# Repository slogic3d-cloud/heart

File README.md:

# <3 LED-Herz

*A heart with a matrix led in heart form.*

Ein herzförmiges PCB mit **46 RGB-LEDs (WS2812B)**, das eine Lichtshow abspielt.
Ein Taster auf der Rückseite schaltet zwischen den Effekten um, Strom kommt per **USB-C**.
Gesteuert wird alles von einem **Seeed XIAO ESP32-C3**, der hinten aufgesteckt ist.

| | |
|---|---|
| Größe | ca. 162 × 153 mm, 2 Lagen, 1,6 mm |
| LEDs | 46 × WS2812B-5050, Raster 16 mm, je ein 100 nF Kondensator |
| Controller | Seeed XIAO ESP32-C3 (oder XIAO ESP32-S3, gleiche Pinbelegung) |
| Strom | USB-C 5 V (nur Strom), Software-Limit 1,5 A |
| Bedienung | 1 Taster: kurz = nächster Effekt, lang = Helligkeit |
| Effekte | Herzschlag, Regenbogen, Wellen, Glitzer, Feuer, Scanner, Konfetti, Auto |

## So funktioniert's

Das ist die vereinfachte Übersicht. Der **echte KiCad-Schaltplan** ist `hardware/heart.kicad_sch`
(als PDF: [docs/schematic.pdf](docs/schematic.pdf)), siehe [Schaltplan in KiCad](#schaltplan-in-kicad).

- **USB-C (J1)** liefert 5 V. Die zwei 5,1 kΩ an CC1/CC2 sagen dem Netzteil: „Ich will 5 V“.
- **+5V** liegt als Kupferfläche auf der ganzen Vorderseite, **GND** als Fläche auf der ganzen Rückseite.
  Dadurch kommen alle LEDs ohne dicke Leiterbahnen an genug Strom.
- Der **XIAO** bekommt seine 5 V über die Schottky-Diode **D47**. Dadurch kannst du den XIAO
  gleichzeitig am PC (zum Flashen) und am Netzteil haben, ohne dass der PC die LEDs versorgen muss.
- Der ESP32 gibt 3,3 V-Signale aus, die WS2812B wollen bei 5 V eigentlich ≥ 3,5 V sehen.
  Der **74AHCT1G125 (U1)** hebt das Datensignal sauber auf 5 V, **R1 (330 Ω)** dämpft die Leitung.
- Die LEDs hängen als **Kette** hintereinander: Start unten an der Spitze, dann in Schlangenlinien nach oben.
  Die Firmware kennt diese Reihenfolge (`src/heart_map.h`), damit Effekte wie „Feuer“ wirklich von unten nach oben laufen.

| Vorderseite (LEDs, +5V-Fläche) | Rückseite (GND-Fläche, XIAO, Taster, Elko) |
|---|---|
|  |  |

## Ordner

```
hardware/
  gen_pcb.py          erzeugt die komplette Platine per Skript (KiCad 7+)
  gen_sch.py          erzeugt den KiCad-Schaltplan
  netlist.py          Bauteil- und Netzliste (gemeinsame Basis für den Schaltplan)
  check_sch.py        prüft: Schaltplan und Platine passen Pin für Pin zusammen
  heart.kicad_pro     KiCad-Projekt – das hier öffnen
  heart.kicad_sch     der Schaltplan
  drc.py              Design-Rule-Check (prüft Abstände, Verbindungen)
  export.py           Gerber + BOM + CPL für JLCPCB
  heart.kicad_pcb     die Platine (mit KiCad öffnen)
  heart.pretty/       eigener Footprint für den XIAO-Sockel
  heart.kicad_sym     eigenes Symbol für den XIAO
  production/         fertige Bestelldateien (heart_gerber.zip, heart_bom.csv, heart_cpl.csv)
src/                  Firmware (PlatformIO / Arduino)
test/test_chain.cpp   prüft, dass Firmware und Platine dieselbe LED-Reihenfolge haben
tools/preview.html    Lichtshow im Browser ansehen, ganz ohne Hardware
cad/gen_case.py       erzeugt Gehäuse, Pixel-Gitter, Diffusor, Tasterstößel und Ständer (CadQuery)
cad/out/              STEP-Dateien für Fusion 360 + 3MF/STL-Dateien zum Drucken
docs/                 Bilder und Schaltplan
JOURNAL.md            Bau-Tagebuch
einkauf/              links.md (Kauflinks) und price.md (alle Preise in € und $), neu erzeugen: python3 tools/einkauf.py
```

**Was kostet das und wo kaufe ich es?** Siehe [einkauf/price.md](einkauf/price.md) (alle Preise in Euro und Dollar)
und [einkauf/links.md](einkauf/links.md) (Kauflinks: BerryBase, Amazon, JLCPCB).
Preise und Dollarkurs werden live abgefragt, mit `python3 tools/einkauf.py` aktualisierst du beides.

## 1. Platine bei JLCPCB bestellen

1. Auf [jlcpcb.com](https://jlcpcb.com) → **Order now** → `hardware/production/heart_gerber.zip` hochladen.
2. Einstellungen: **2 Layers**, Dicke **1.6 mm**, Farbe nach Wahl (Rot oder Schwarz sieht beim Herz gut aus),
   Surface Finish **HASL (lead free)** reicht.
3. Unten **PCB Assembly** einschalten → **Assemble top side**, Stückzahl z. B. 2 (Minimum bei Bestückung).
4. **BOM** = `hardware/production/heart_bom.csv`, **CPL** = `hardware/production/heart_cpl.csv` hochladen.
5. Im Bauteil-Check sollten alle 8 Positionen gefunden werden (LCSC-Nummern sind drin, geprüft im Oktober 2026):

   | Teil | Menge | LCSC |
   |---|---|---|
   | WS2812B-B/W (5050) | 46 | C114586 |
   | 100 nF 0603 | 47 | C14663 |
   | 10 µF 0805 | 1 | C15850 |
   | 5,1 kΩ 0603 | 2 | C23186 |
   | 330 Ω 0603 | 1 | C23138 |
   | SN74AHCT1G125DBVR | 1 | C7484 |
   | SS34 (SMA) | 1 | C408258 |
   | USB-C HRO TYPE-C-31-M-12 | 1 | C165948 |

6. **Ganz wichtig: Bestückungs-Vorschau anschauen!** JLCPCB zeigt die Bauteile über der Platine an.
   Bei manchen Bauteilen (oft LEDs, SOT-23, USB-C) dreht JLCPCB anders als KiCad.
   Prüfe vor allem:
   - **LEDs:** die abgeschrägte Ecke / Markierung muss bei **Pin 1** sein (im KiCad-Footprint die „1“ im Aufdruck).
   - **U1:** Pin 1 ist der Pin links oben, wenn die 2-Pin-Seite rechts ist.
   - **D47:** der Strich (Kathode) zeigt zum XIAO hin.
   Falsch gedrehte Teile kannst du direkt in der Vorschau drehen.
7. Preis: Die Platine ist größer als 10 × 10 cm und einige Bauteile sind „Extended Parts“
   (Bestückungsgebühr pro Bauteilsorte). Schau dir das Angebot genau an, bevor du bestellst.

### Was du selbst lötest (alles Durchsteck-Teile, auf der Rückseite)

| Teil | Wo | Hinweis |
|---|---|---|
| Seeed XIAO ESP32-C3 | U2 | mit 2 × 7-poligen Stiftleisten am XIAO |
| 2 × Buchsenleiste 1×7, 2,54 mm | U2 | auf die Platine löten, XIAO steckt drauf. **Bauteile des XIAO zeigen von der Platine weg, seine USB-C-Buchse zur Ausbuchtung im aufgedruckten Rahmen** |
| Taster 6 × 6 mm (THT) | SW1 „EFFEKT“ | |
| Elko 1000 µF (10 V oder mehr, z. B. 25 V), Ø 10 mm, Raster 5 mm, max. 20 mm hoch | C50 | **Polung!** Das eckige Pad ist Plus |

Tipp: Erst Buchsenleisten, dann Taster, zuletzt den Elko löten.

## 2. Firmware flashen

Mit [PlatformIO](https://platformio.org) (VS Code-Erweiterung oder `pip install platformio`):

```bash
pio run -e xiao_esp32c3 -t upload    # flashen
pio device monitor                   # Ausgabe ansehen (115200 Baud)
```

Falls der Upload nicht klappt: am XIAO **BOOT** gedrückt halten, **RESET** kurz drücken, BOOT loslassen, nochmal hochladen.

Mit der **Arduino IDE** geht es auch: Board „XIAO_ESP32C3“ auswählen, Bibliothek **FastLED** installieren,
alle Dateien aus `src/` in einen Sketch-Ordner `heart/` kopieren und `main.cpp` in `heart.ino` umbenennen.

Beim Einschalten läuft einmal ein Regenbogen durch alle 46 LEDs in Ketten-Reihenfolge.
Bleibt er an einer Stelle hängen, hat die LED davor oder genau diese ein Lötproblem.

## 3. Bedienung

- **Kurz drücken:** nächster Effekt. Nach „Konfetti“ kommt **Auto** (wechselt alle 15 s).
- **Lang drücken (0,8 s):** Helligkeit 24 → 64 → 128 → 200.
- Effekt und Helligkeit bleiben gespeichert, auch nach dem Ausstecken.

Einstellungen (Pins, Stromlimit, Helligkeitsstufen, Auto-Zeit) stehen in `src/config.h`.
Neue Effekte schreibst du in `src/effects.cpp` und trägst sie unten in `LIST` ein.

## 4. Effekte ohne Hardware ansehen

`tools/preview.html` im Browser öffnen. Die Vorschau benutzt dieselbe LED-Anordnung und dieselben Effekte.

| Regenbogen | Feuer |
|---|---|
|  |  |

## Schaltplan in KiCad

1. KiCad 7 oder neuer installieren ([kicad.org](https://www.kicad.org/download/)).
2. `hardware/heart.kicad_pro` öffnen. Im Projektfenster:
   - **Schaltplan-Editor** → `heart.kicad_sch` (ein A2-Blatt: oben Strom, XIAO, Pegelwandler; unten die 46 LEDs)
   - **Leiterplatten-Editor** → `heart.kicad_pcb`
3. Die Bibliotheken `heart` (XIAO-Symbol und -Footprint) sind über `sym-lib-table` / `fp-lib-table`
   im Projektordner eingebunden, da musst du nichts einstellen.

Verbunden wird im Schaltplan über **Netzlabels** (z. B. `LED5_DOUT`, `DATA_5V`) und die Power-Symbole
`+5V` / `GND`. Gleicher Name = gleiche Leitung. Die Namen sind exakt dieselben wie auf der Platine.

Schaltplan und Platine sind **verknüpft**. Wenn du im Schaltplan etwas änderst (z. B. einen Wert),
kannst du im Leiterplatten-Editor **Werkzeuge → Leiterplatte aus Schaltplan aktualisieren (F8)** drücken.
Geprüft wird das mit:

```bash
python3 hardware/check_sch.py   # "OK: Schaltplan und Platine stimmen überein"
```

KiCad 8/9 fragt beim Öffnen evtl., ob die Dateien ins neue Format umgewandelt werden sollen. Das ist ok.

## Gehäuse und Ständer (Fusion 360 / 3D-Druck)

| Im Ständer | Rückseite |
|---|---|
|  |  |

Alle Teile liegen in `cad/out/`, jeweils als **STEP** (für Fusion 360) und als **3MF** und **STL** (zum Drucken).
Die Druckdateien liegen schon flach auf dem Druckbett (Unterseite bei z = 0), die STEP-Dateien in Einbauposition.

| Datei | Teil | Material-Tipp |
|---|---|---|
| `heart_case_shell` | Rückschale mit Abstandshaltern, USB-C-Schlitz, Fenster fürs XIAO-Kabel, Tasterloch, 2 Schlüssellöchern | PLA/PETG, Farbe nach Wahl |
| `heart_case_grid` | Pixel-Gitter (16-mm-Raster, 10 mm tief), jede LED leuchtet in ihrem eigenen Quadrat | **schwarz**, damit kein Licht in die Nachbarzelle scheint |
| `heart_case_diffuser` | 1-mm-Platte vorne, macht aus den LED-Punkten gleichmäßige Pixel | weiß/transluzent. Alternative: Transparentpapier oder milchige Acrylplatte in Herzform |
| `heart_case_button_plunger` | Stößel: drückt von hinten auf den Taster | beliebig |
| `heart_stand` | Ständer für den Tisch, Herzspitze sitzt in einer 90°-V-Tasche, 10° nach hinten geneigt | beliebig |
| `heart_case_assembly.step` | alles zusammengebaut, inkl. Platine (nur zum Anschauen) | – |
| `heart_pcb.step` | die Platine aus KiCad | – |

**In Fusion 360 öffnen:** *Datei → Öffnen → Von meinem Computer…* → `.step`-Datei wählen.
Fusion lädt die Datei in die Cloud hoch und öffnet sie. Die Teile sind „dumme“ Volumenkörper
(ohne Verlauf). Ändern kannst du sie trotzdem direkt, z. B. mit *Fläche verschieben* (*Press Pull*).
Für größere Änderungen lieber die Maße oben in `cad/gen_case.py` anpassen und neu erzeugen:

```bash
pip install cadquery
python3 cad/gen_case.py     # baut alle Teile neu und prüft auf Kollisionen mit den Bauteilen
```

**Ohne eigenen 3D-Drucker:** Die 3MF- (oder STL-)Dateien bei einem Druckdienst hochladen, z. B. bei
JLCPCB (bietet auch 3D-Druck an) oder einem anderen Online-Druckdienst.
FDM-Druck in PLA ist am günstigsten. Die Rückschale und das Gitter sind die großen Teile,
schau dir den Preis an, bevor du bestellst.

**Zusammenbau:**
1. Tasterstößel von innen durch das Loch in der Rückwand stecken (der Kragen bleibt innen).
2. Platine einlegen: Die USB-C-Buchse gehört in den Schlitz an der linken unteren Kante.
   Mit **3 Schrauben** durch die Befestigungslöcher in die Abstandshalter schrauben
   (Kunststoff-/Blechschrauben ca. 2,9 × 9,5 mm, oder M3 × 8, die sich ins 2,5-mm-Loch schneiden).
3. Pixel-Gitter einlegen (liegt auf der umlaufenden Kante, 4 mm über der Platine).
4. Diffusor oben drauflegen (bei Bedarf mit ein paar Tropfen Kleber fixieren).
5. Zum Flashen kommst du durch das Fenster in der Rückwand mit dem USB-Kabel an den XIAO.

Maße: Gehäuse 167 × 158 × 41 mm. Hinter der Platine sind 22 mm Platz (XIAO auf Buchsenleisten,
Elko bis 20 mm hoch). Der Stößel ist für einen 6 × 6-mm-Taster mit 4,9 mm Höhe ausgelegt.
Ist dein Taster anders hoch, `BUTTON_H` in `cad/gen_case.py` ändern.

## 5. Platine selbst ändern

Die Platine wird komplett von `hardware/gen_pcb.py` erzeugt (Herzform, Bauteile, Leiterbahnen, Kupferflächen).
Du brauchst KiCad 7 oder neuer (mit Python).

```bash
python3 hardware/gen_sch.py     # Schaltplan neu erzeugen
python3 hardware/gen_pcb.py     # Platine neu erzeugen
python3 hardware/check_sch.py   # Schaltplan == Platine?
python3 hardware/drc.py         # prüfen: muss "0 unconnected pads" und keine Fehler zeigen
python3 hardware/export.py      # Bestelldateien neu bauen
g++ -std=c++11 -Isrc test/test_chain.cpp -o /tmp/t && /tmp/t   # Firmware passt zur Platine?
```

Du kannst Schaltplan und Platine natürlich auch direkt in KiCad von Hand weiterbearbeiten.
Dann aber `gen_sch.py` / `gen_pcb.py` nicht mehr laufen lassen, sonst werden deine Änderungen überschrieben.

Aktueller DRC-Stand: 0 Fehler, 0 offene Verbindungen. Es bleibt eine gewollte Warnung:
Beim USB-C-Footprint wurde der Bestückungsdruck entfernt, weil er über den Platinenrand ragen würde.

## Tipps und Fehlersuche

- **Strom:** Volle Helligkeit in Weiß zieht fast 3 A. Das Software-Limit steht auf 1,5 A.
  Mit einem guten 5 V/3 A-Netzteil kannst du `POWER_MILLIAMPS` in `src/config.h` auf 2500 erhöhen.
- **Nur die ersten LEDs gehen:** Lötstelle an der ersten dunklen LED oder an der davor prüfen.
- **Farben vertauscht (Rot ↔ Grün):** in `src/config.h` `COLOR_ORDER` auf `RGB` ändern.
- **Gar nichts leuchtet:** Steckt der XIAO richtig herum? Ist das Netzteil eingesteckt
  (über den XIAO-USB allein bekommen die LEDs keinen Strom, das ist Absicht)?
- **Flackern:** Elko C50 richtig herum eingelötet?

## Lizenz

MIT, siehe [LICENSE](LICENSE).

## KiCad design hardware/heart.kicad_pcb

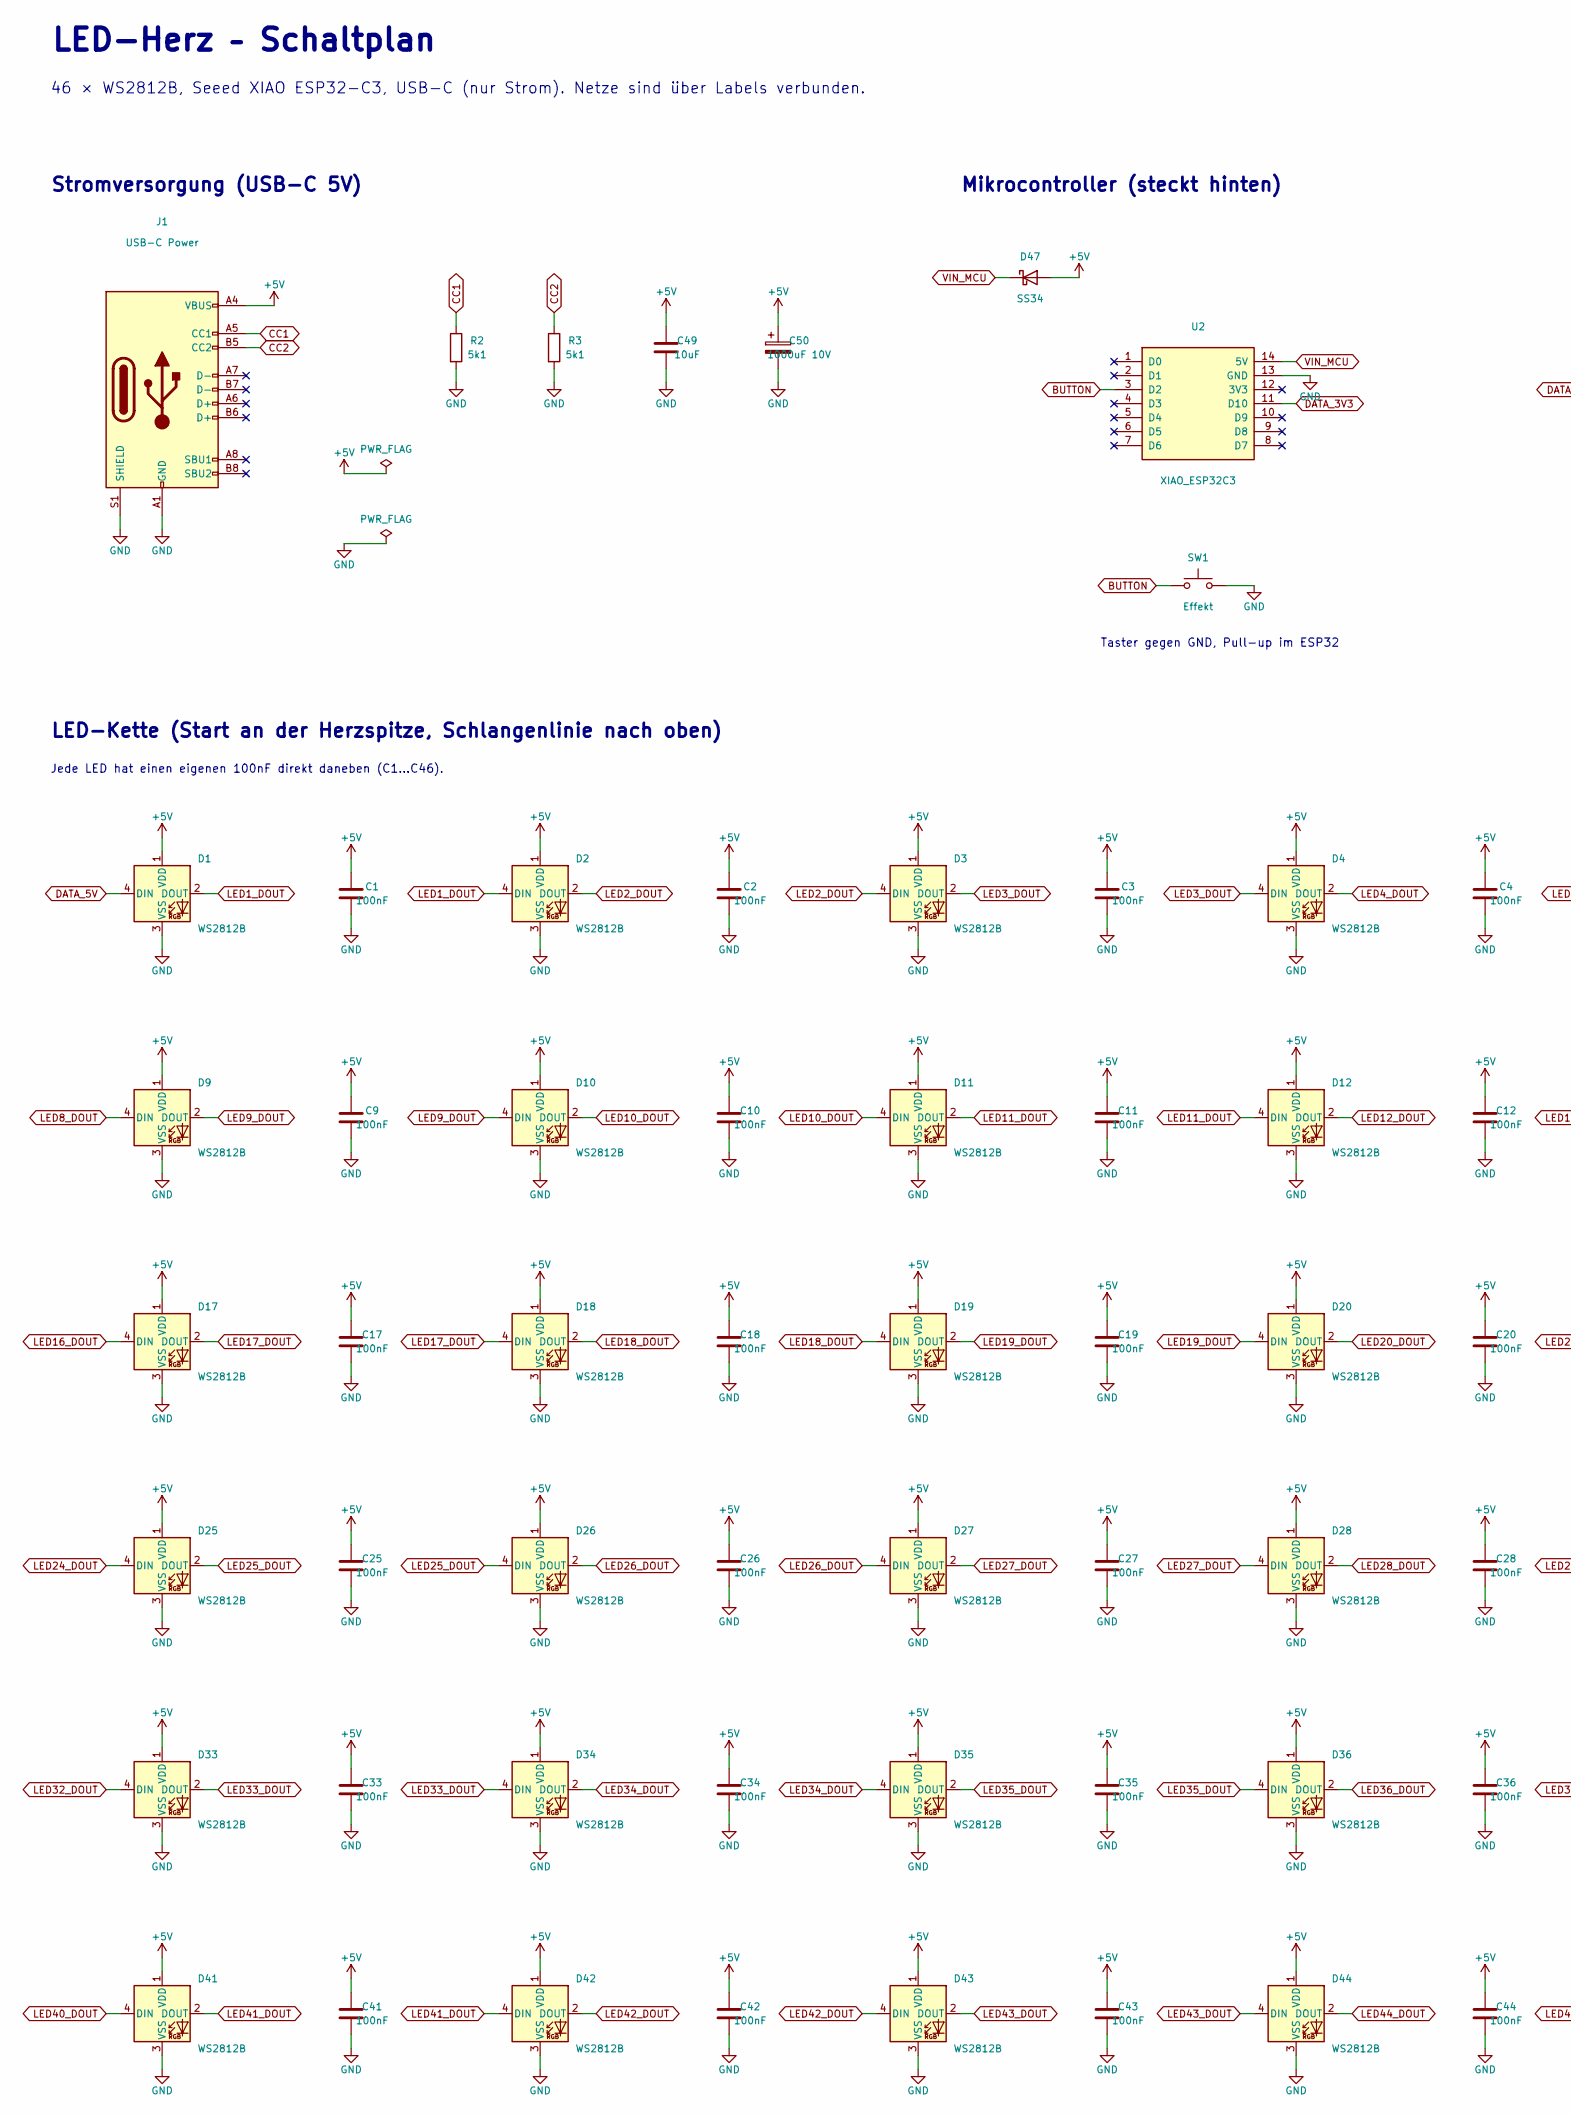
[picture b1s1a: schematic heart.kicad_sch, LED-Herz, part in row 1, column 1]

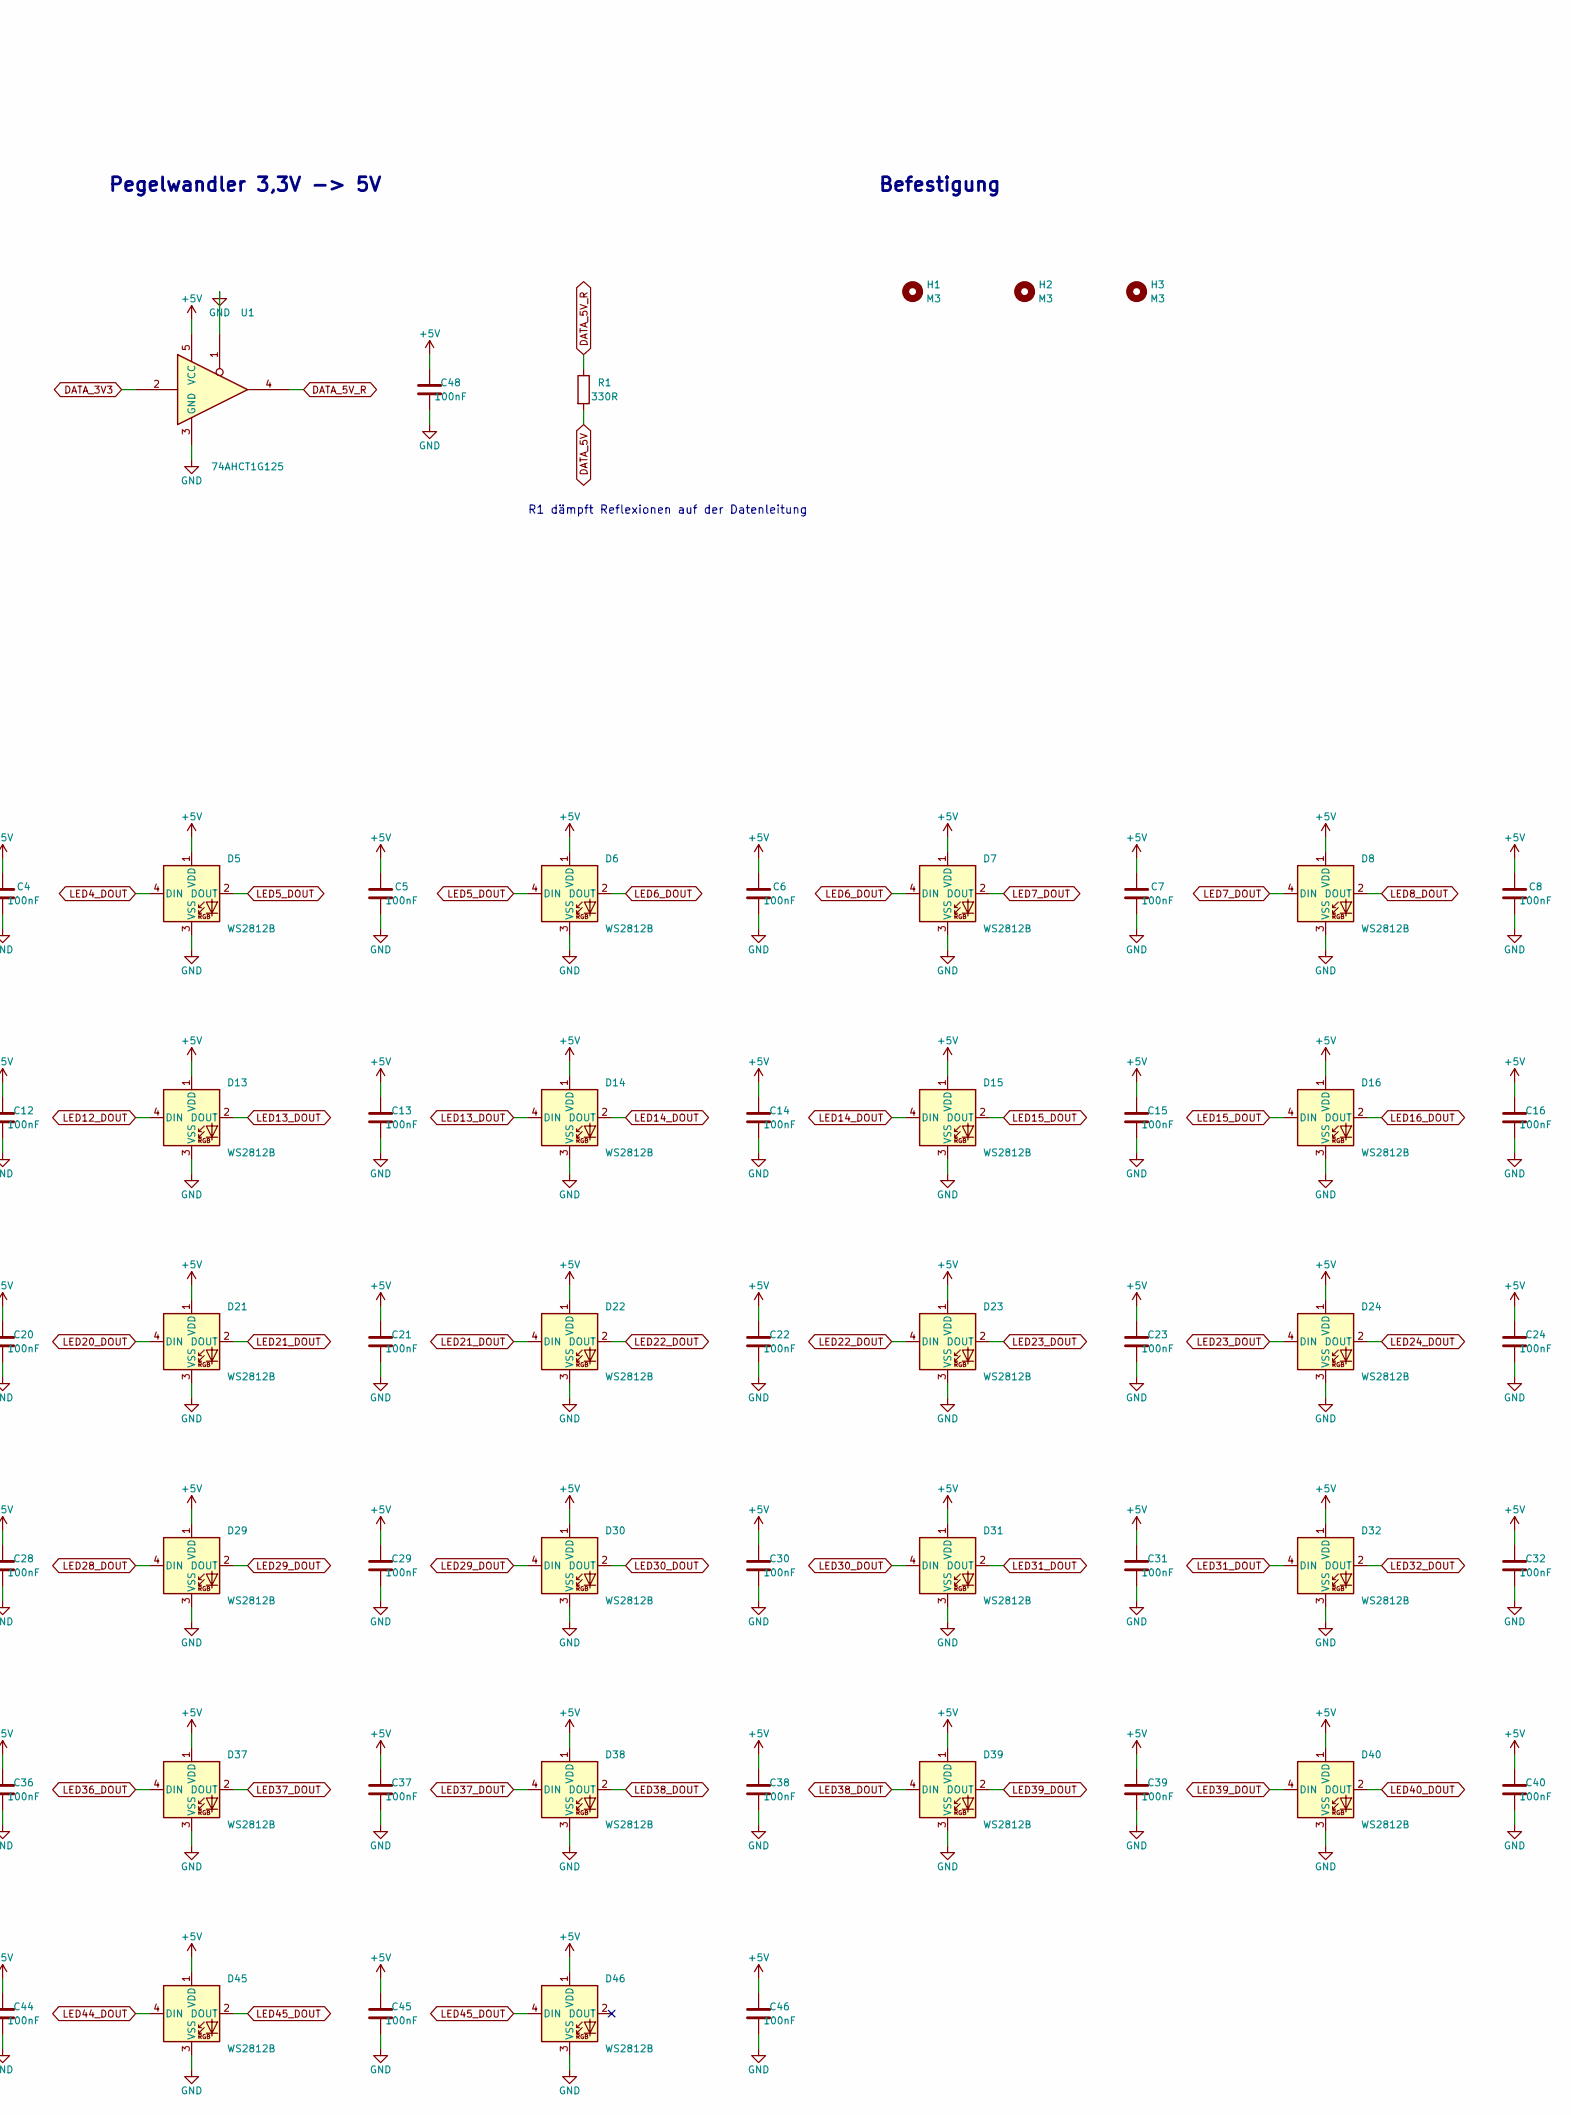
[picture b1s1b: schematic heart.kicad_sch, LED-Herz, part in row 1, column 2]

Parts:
C1, C2, C3, C4, C5, C6, C7, C8, C9, C10, C11, C12, C13, C14, C15, C16, C17, C18, C19, C20, C21, C22, C23, C24, C25, C26, C27, C28, C29, C30, C31, C32, C33, C34, C35, C36, C37, C38, C39, C40, C41, C42, C43, C44, C45, C46, C48: 100nF; C_0603_1608Metric; LCSC C14663
C49: 10uF; C_0805_2012Metric; LCSC C15850
C50: 1000uF 10V; CP_Radial_D10.0mm_P5.00mm
D1, D2, D3, D4, D5, D6, D7, D8, D9, D10, D11, D12, D13, D14, D15, D16, D17, D18, D19, D20, D21, D22, D23, D24, D25, D26, D27, D28, D29, D30, D31, D32, D33, D34, D35, D36, D37, D38, D39, D40, D41, D42, D43, D44, D45, D46: WS2812B; LED_WS2812B_PLCC4_5.0x5.0mm_P3.2mm; LCSC C114586
D47: SS34; D_SMA; LCSC C408258
H1, H2, H3: M3; MountingHole_3.2mm_M3
J1: USB-C Power; USB_C_Receptacle_HRO_TYPE-C-31-M-12; LCSC C165948
R1: 330R; R_0603_1608Metric; LCSC C23138
R2, R3: 5k1; R_0603_1608Metric; LCSC C23186
SW1: Effekt; SW_PUSH_6mm
U1: 74AHCT1G125; SOT-23-5; LCSC C7484
U2: XIAO_ESP32C3; Seeed_XIAO_Socket

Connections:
+5V: C1.1, C2.1, C3.1, C4.1, C5.1, C6.1, C7.1, C8.1, C9.1, C10.1, C11.1, C12.1, C13.1, C14.1, C15.1, C16.1, C17.1, C18.1, C19.1, C20.1, C21.1, C22.1, C23.1, C24.1, C25.1, C26.1, C27.1, C28.1, C29.1, C30.1, C31.1, C32.1, C33.1, C34.1, C35.1, C36.1, C37.1, C38.1, C39.1, C40.1, C41.1, C42.1, C43.1, C44.1, C45.1, C46.1, C48.1, C49.1, C50.1, D1.1 (VDD), D2.1 (VDD), D3.1 (VDD), D4.1 (VDD), D5.1 (VDD), D6.1 (VDD), D7.1 (VDD), D8.1 (VDD), D9.1 (VDD), D10.1 (VDD), D11.1 (VDD), D12.1 (VDD), D13.1 (VDD), D14.1 (VDD), D15.1 (VDD), D16.1 (VDD), D17.1 (VDD), D18.1 (VDD), D19.1 (VDD), D20.1 (VDD), D21.1 (VDD), D22.1 (VDD), D23.1 (VDD), D24.1 (VDD), D25.1 (VDD), D26.1 (VDD), D27.1 (VDD), D28.1 (VDD), D29.1 (VDD), D30.1 (VDD), D31.1 (VDD), D32.1 (VDD), D33.1 (VDD), D34.1 (VDD), D35.1 (VDD), D36.1 (VDD), D37.1 (VDD), D38.1 (VDD), D39.1 (VDD), D40.1 (VDD), D41.1 (VDD), D42.1 (VDD), D43.1 (VDD), D44.1 (VDD), D45.1 (VDD), D46.1 (VDD), D47.2 (A), J1.A4 (VBUS), J1.A9 (VBUS), J1.B4 (VBUS), J1.B9 (VBUS), U1.5 (VCC)
BUTTON: SW1.1, U2.3 (D2)
CC1: J1.A5 (CC1), R2.1
CC2: J1.B5 (CC2), R3.1
DATA_3V3: U1.2, U2.11 (D10)
DATA_5V: D1.4 (DIN), R1.2
DATA_5V_R: R1.1, U1.4
GND: C1.2, C2.2, C3.2, C4.2, C5.2, C6.2, C7.2, C8.2, C9.2, C10.2, C11.2, C12.2, C13.2, C14.2, C15.2, C16.2, C17.2, C18.2, C19.2, C20.2, C21.2, C22.2, C23.2, C24.2, C25.2, C26.2, C27.2, C28.2, C29.2, C30.2, C31.2, C32.2, C33.2, C34.2, C35.2, C36.2, C37.2, C38.2, C39.2, C40.2, C41.2, C42.2, C43.2, C44.2, C45.2, C46.2, C48.2, C49.2, C50.2, D1.3 (VSS), D2.3 (VSS), D3.3 (VSS), D4.3 (VSS), D5.3 (VSS), D6.3 (VSS), D7.3 (VSS), D8.3 (VSS), D9.3 (VSS), D10.3 (VSS), D11.3 (VSS), D12.3 (VSS), D13.3 (VSS), D14.3 (VSS), D15.3 (VSS), D16.3 (VSS), D17.3 (VSS), D18.3 (VSS), D19.3 (VSS), D20.3 (VSS), D21.3 (VSS), D22.3 (VSS), D23.3 (VSS), D24.3 (VSS), D25.3 (VSS), D26.3 (VSS), D27.3 (VSS), D28.3 (VSS), D29.3 (VSS), D30.3 (VSS), D31.3 (VSS), D32.3 (VSS), D33.3 (VSS), D34.3 (VSS), D35.3 (VSS), D36.3 (VSS), D37.3 (VSS), D38.3 (VSS), D39.3 (VSS), D40.3 (VSS), D41.3 (VSS), D42.3 (VSS), D43.3 (VSS), D44.3 (VSS), D45.3 (VSS), D46.3 (VSS), J1.A1 (GND), J1.A12 (GND), J1.B1 (GND), J1.B12 (GND), J1.S1 (SHIELD), R2.2, R3.2, SW1.2, U1.1, U1.3 (GND), U2.13 (GND)
LED1_DOUT: D1.2 (DOUT), D2.4 (DIN)
LED2_DOUT: D2.2 (DOUT), D3.4 (DIN)
LED3_DOUT: D3.2 (DOUT), D4.4 (DIN)
LED4_DOUT: D4.2 (DOUT), D5.4 (DIN)
LED5_DOUT: D5.2 (DOUT), D6.4 (DIN)
LED6_DOUT: D6.2 (DOUT), D7.4 (DIN)
LED7_DOUT: D7.2 (DOUT), D8.4 (DIN)
LED8_DOUT: D8.2 (DOUT), D9.4 (DIN)
LED9_DOUT: D9.2 (DOUT), D10.4 (DIN)
LED10_DOUT: D10.2 (DOUT), D11.4 (DIN)
LED11_DOUT: D11.2 (DOUT), D12.4 (DIN)
LED12_DOUT: D12.2 (DOUT), D13.4 (DIN)
LED13_DOUT: D13.2 (DOUT), D14.4 (DIN)
LED14_DOUT: D14.2 (DOUT), D15.4 (DIN)
LED15_DOUT: D15.2 (DOUT), D16.4 (DIN)
LED16_DOUT: D16.2 (DOUT), D17.4 (DIN)
LED17_DOUT: D17.2 (DOUT), D18.4 (DIN)
LED18_DOUT: D18.2 (DOUT), D19.4 (DIN)
LED19_DOUT: D19.2 (DOUT), D20.4 (DIN)
LED20_DOUT: D20.2 (DOUT), D21.4 (DIN)
LED21_DOUT: D21.2 (DOUT), D22.4 (DIN)
LED22_DOUT: D22.2 (DOUT), D23.4 (DIN)
LED23_DOUT: D23.2 (DOUT), D24.4 (DIN)
LED24_DOUT: D24.2 (DOUT), D25.4 (DIN)
LED25_DOUT: D25.2 (DOUT), D26.4 (DIN)
LED26_DOUT: D26.2 (DOUT), D27.4 (DIN)
LED27_DOUT: D27.2 (DOUT), D28.4 (DIN)
LED28_DOUT: D28.2 (DOUT), D29.4 (DIN)
LED29_DOUT: D29.2 (DOUT), D30.4 (DIN)
LED30_DOUT: D30.2 (DOUT), D31.4 (DIN)
LED31_DOUT: D31.2 (DOUT), D32.4 (DIN)
LED32_DOUT: D32.2 (DOUT), D33.4 (DIN)
LED33_DOUT: D33.2 (DOUT), D34.4 (DIN)
LED34_DOUT: D34.2 (DOUT), D35.4 (DIN)
LED35_DOUT: D35.2 (DOUT), D36.4 (DIN)
LED36_DOUT: D36.2 (DOUT), D37.4 (DIN)
LED37_DOUT: D37.2 (DOUT), D38.4 (DIN)
LED38_DOUT: D38.2 (DOUT), D39.4 (DIN)
LED39_DOUT: D39.2 (DOUT), D40.4 (DIN)
LED40_DOUT: D40.2 (DOUT), D41.4 (DIN)
LED41_DOUT: D41.2 (DOUT), D42.4 (DIN)
LED42_DOUT: D42.2 (DOUT), D43.4 (DIN)
LED43_DOUT: D43.2 (DOUT), D44.4 (DIN)
LED44_DOUT: D44.2 (DOUT), D45.4 (DIN)
LED45_DOUT: D45.2 (DOUT), D46.4 (DIN)
VIN_MCU: D47.1 (K), U2.14 (5V)

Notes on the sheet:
LED-Herz – Schaltplan
46 × WS2812B, Seeed XIAO ESP32-C3, USB-C (nur Strom). Netze sind über Labels verbunden.
Stromversorgung (USB-C 5V)
Mikrocontroller (steckt hinten)
Taster gegen GND, Pull-up im ESP32
Pegelwandler 3,3V -> 5V
R1 dämpft Reflexionen auf der Datenleitung
Befestigung
LED-Kette (Start an der Herzspitze, Schlangenlinie nach oben)
Jede LED hat einen eigenen 100nF direkt daneben (C1…C46).

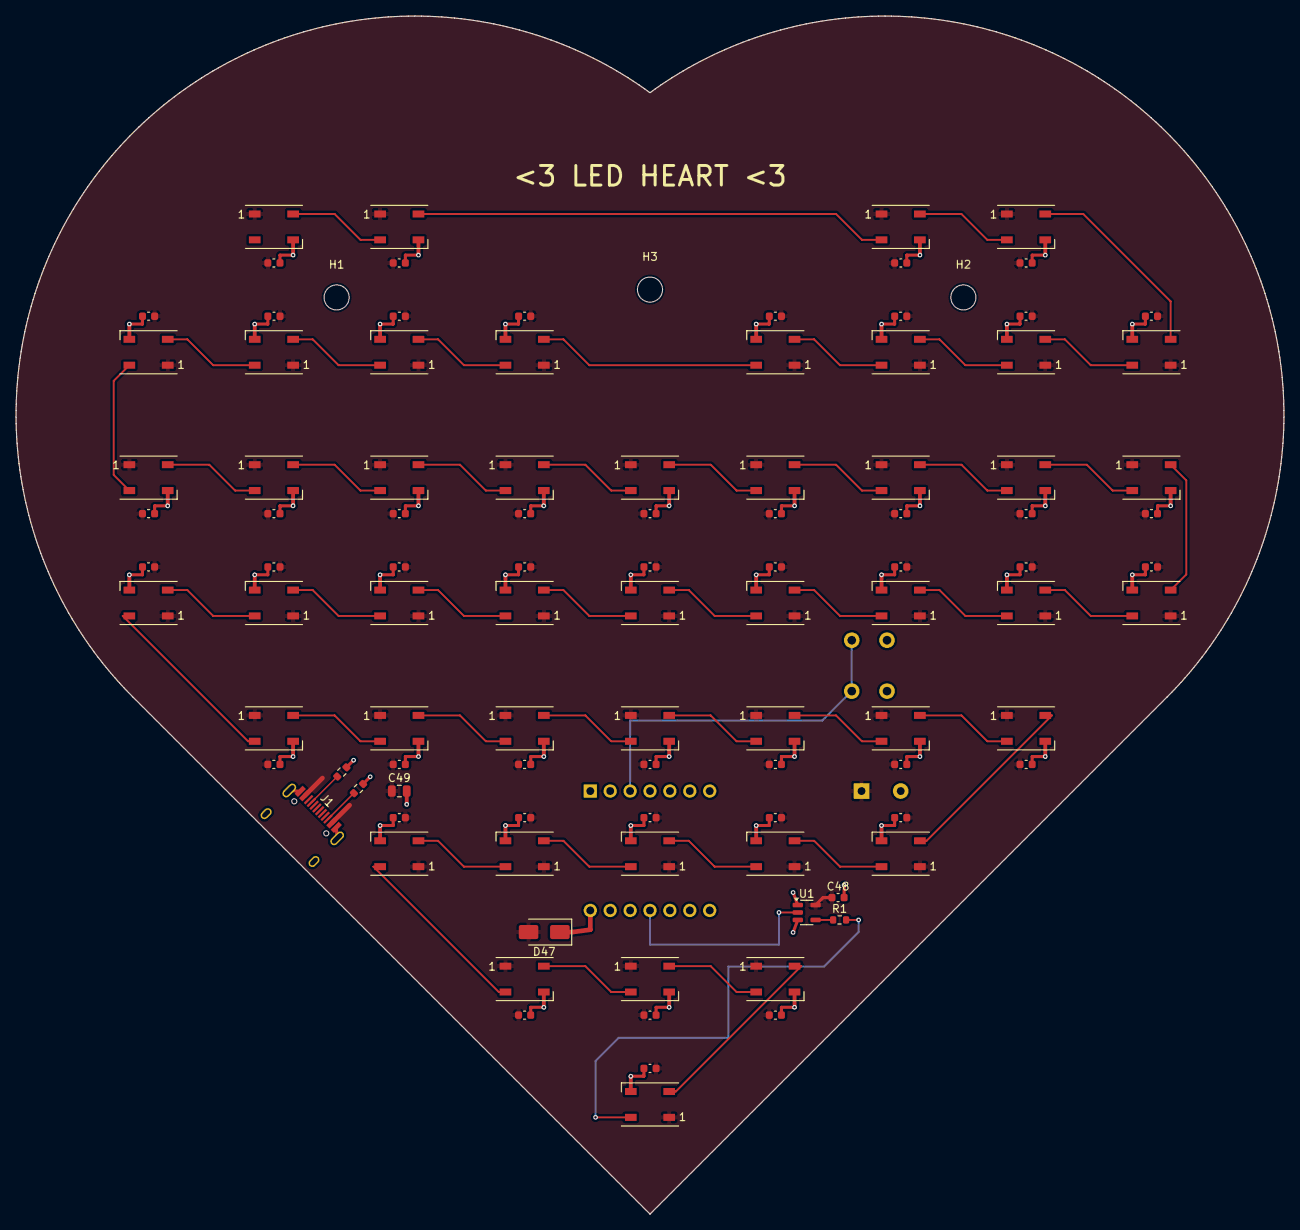
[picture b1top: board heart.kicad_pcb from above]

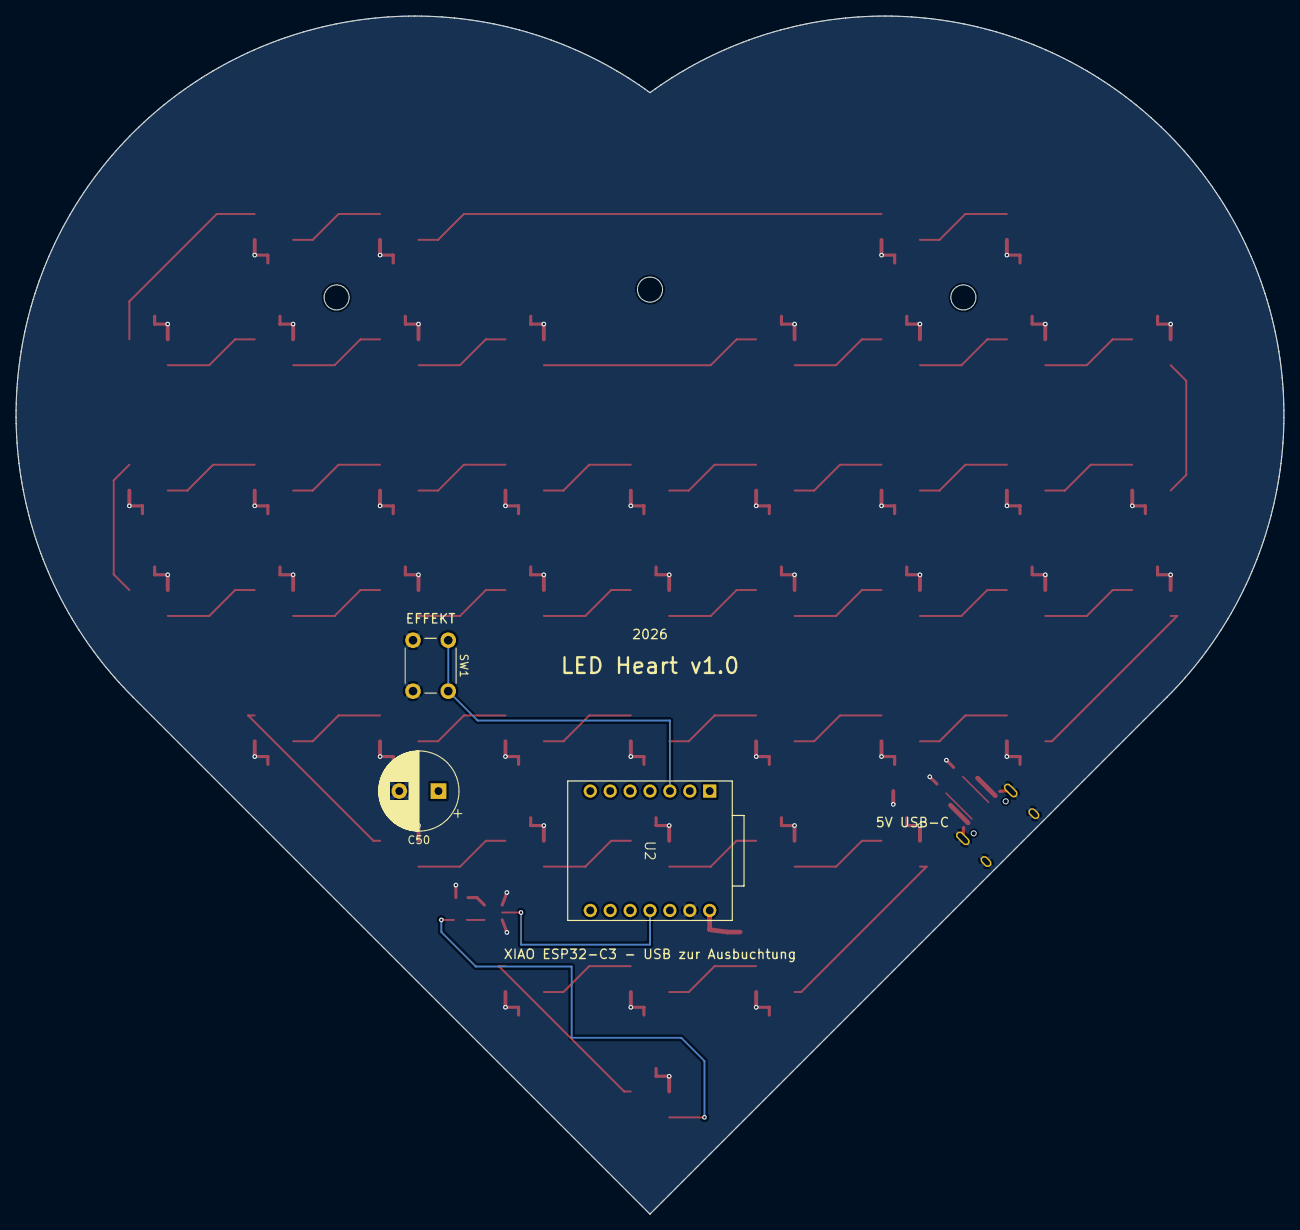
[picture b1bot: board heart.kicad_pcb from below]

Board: 2 copper layers, 161.8 x 152.9 mm, 106 parts (3 on the bottom side), 54 nets.

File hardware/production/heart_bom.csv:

Comment,Designator,Footprint,LCSC Part #
100nF 50V X7R 0603,"C1,C2,C3,C4,C5,C6,C7,C8,C9,C10,C11,C12,C13,C14,C15,C16,C17,C18,C19,C20,C21,C22,C23,C24,C25,C26,C27,C28,C29,C30,C31,C32,C33,C34,C35,C36,C37,C38,C39,C40,C41,C42,C43,C44,C45,C46,C48",C_0603_1608Metric,C14663
10uF 25V X5R 0805,C49,C_0805_2012Metric,C15850
330R 1% 0603,R1,R_0603_1608Metric,C23138
5.1k 1% 0603,"R2,R3",R_0603_1608Metric,C23186
SN74AHCT1G125DBVR,U1,SOT-23-5,C7484
SS34 Schottky 40V 3A SMA,D47,D_SMA,C408258
HRO TYPE-C-31-M-12,J1,USB_C_Receptacle_HRO_TYPE-C-31-M-12,C165948
WS2812B-B/W 5050 RGB LED,"D1,D2,D3,D4,D5,D6,D7,D8,D9,D10,D11,D12,D13,D14,D15,D16,D17,D18,D19,D20,D21,D22,D23,D24,D25,D26,D27,D28,D29,D30,D31,D32,D33,D34,D35,D36,D37,D38,D39,D40,D41,D42,D43,D44,D45,D46",LED_WS2812B_PLCC4_5.0x5.0mm_P3.2mm,C114586
